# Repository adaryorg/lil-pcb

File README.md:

mini pcb for a pro micro controller

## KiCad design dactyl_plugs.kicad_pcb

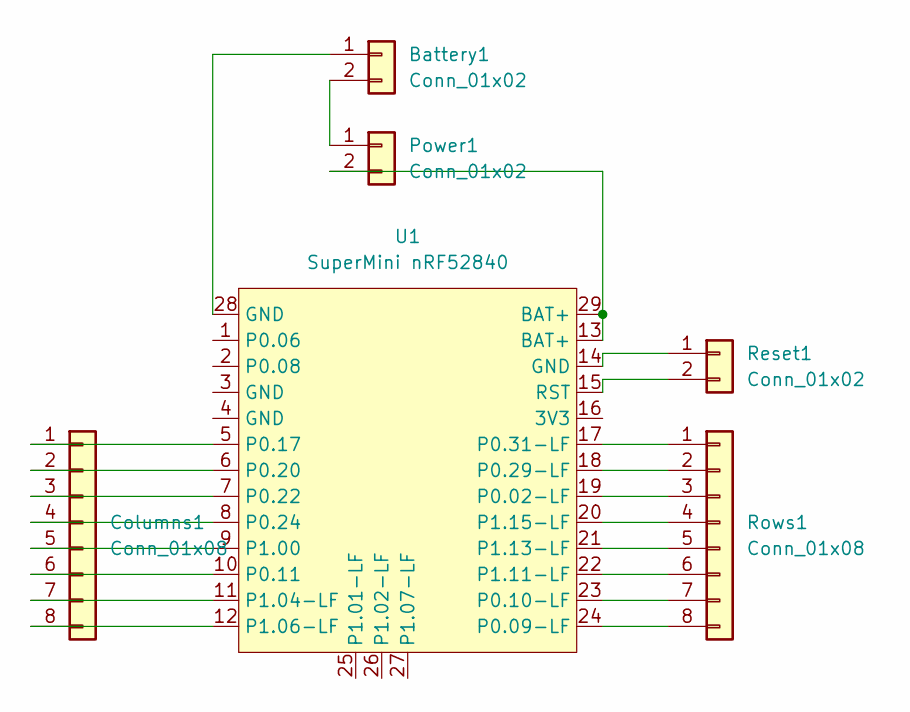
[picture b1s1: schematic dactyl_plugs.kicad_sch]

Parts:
Battery1: Conn_01x02; JST_PH_B2B-PH-K_1x02_P2.00mm_Vertical
Columns1: Conn_01x08; JST_PH_B8B-PH-K_1x08_P2.00mm_Vertical
Power1: Conn_01x02; JST_PH_B2B-PH-K_1x02_P2.00mm_Vertical
Reset1: Conn_01x02; JST_PH_B2B-PH-K_1x02_P2.00mm_Vertical
Rows1: Conn_01x08; JST_PH_B8B-PH-K_1x08_P2.00mm_Vertical
U1: SuperMini nRF52840; SuperMini_nRF52840_AH_USBup

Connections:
unnamed: Battery1.1, U1.28 (GND)
unnamed: Battery1.2, Power1.1
unnamed: Columns1.1, U1.5 (P0.17)
unnamed: Columns1.2, U1.6 (P0.20)
unnamed: Columns1.3, U1.7 (P0.22)
unnamed: Columns1.4, U1.8 (P0.24)
unnamed: Columns1.5, U1.9 (P1.00)
unnamed: Columns1.6, U1.10 (P0.11)
unnamed: Columns1.7, U1.11 (P1.04-LF)
unnamed: Columns1.8, U1.12 (P1.06-LF)
unnamed: Power1.2, U1.13 (BAT+), U1.29 (BAT+)
unnamed: Reset1.1, U1.14 (GND)
unnamed: Reset1.2, U1.15 (RST)
unnamed: Rows1.1, U1.17 (P0.31-LF)
unnamed: Rows1.2, U1.18 (P0.29-LF)
unnamed: Rows1.3, U1.19 (P0.02-LF)
unnamed: Rows1.4, U1.20 (P1.15-LF)
unnamed: Rows1.5, U1.21 (P1.13-LF)
unnamed: Rows1.6, U1.22 (P1.11-LF)
unnamed: Rows1.7, U1.23 (P0.10-LF)
unnamed: Rows1.8, U1.24 (P0.09-LF)

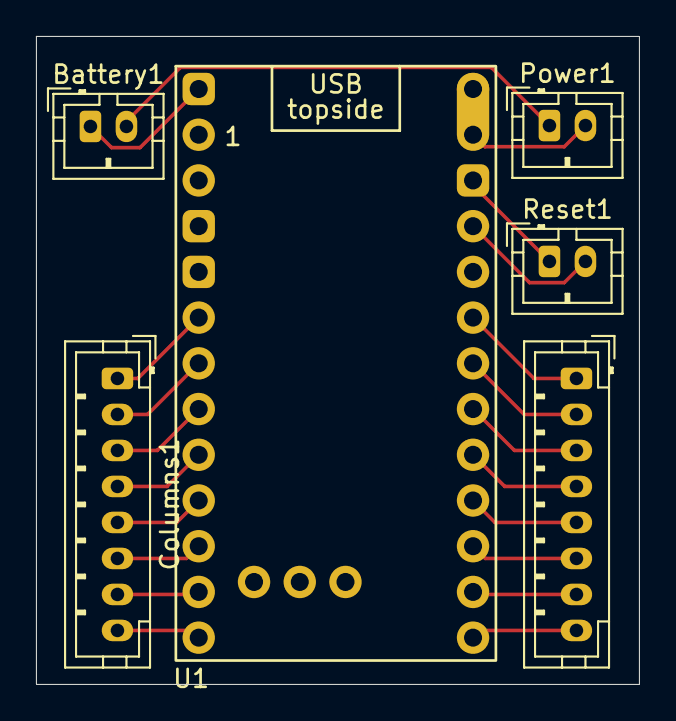
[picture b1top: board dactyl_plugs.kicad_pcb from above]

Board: 2 copper layers, 33.5 x 36.0 mm, 6 parts (0 on the bottom side), 21 nets.

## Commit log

2025-10-25 Add description for mini PCB project
2025-10-25 Add MIT License to the project
